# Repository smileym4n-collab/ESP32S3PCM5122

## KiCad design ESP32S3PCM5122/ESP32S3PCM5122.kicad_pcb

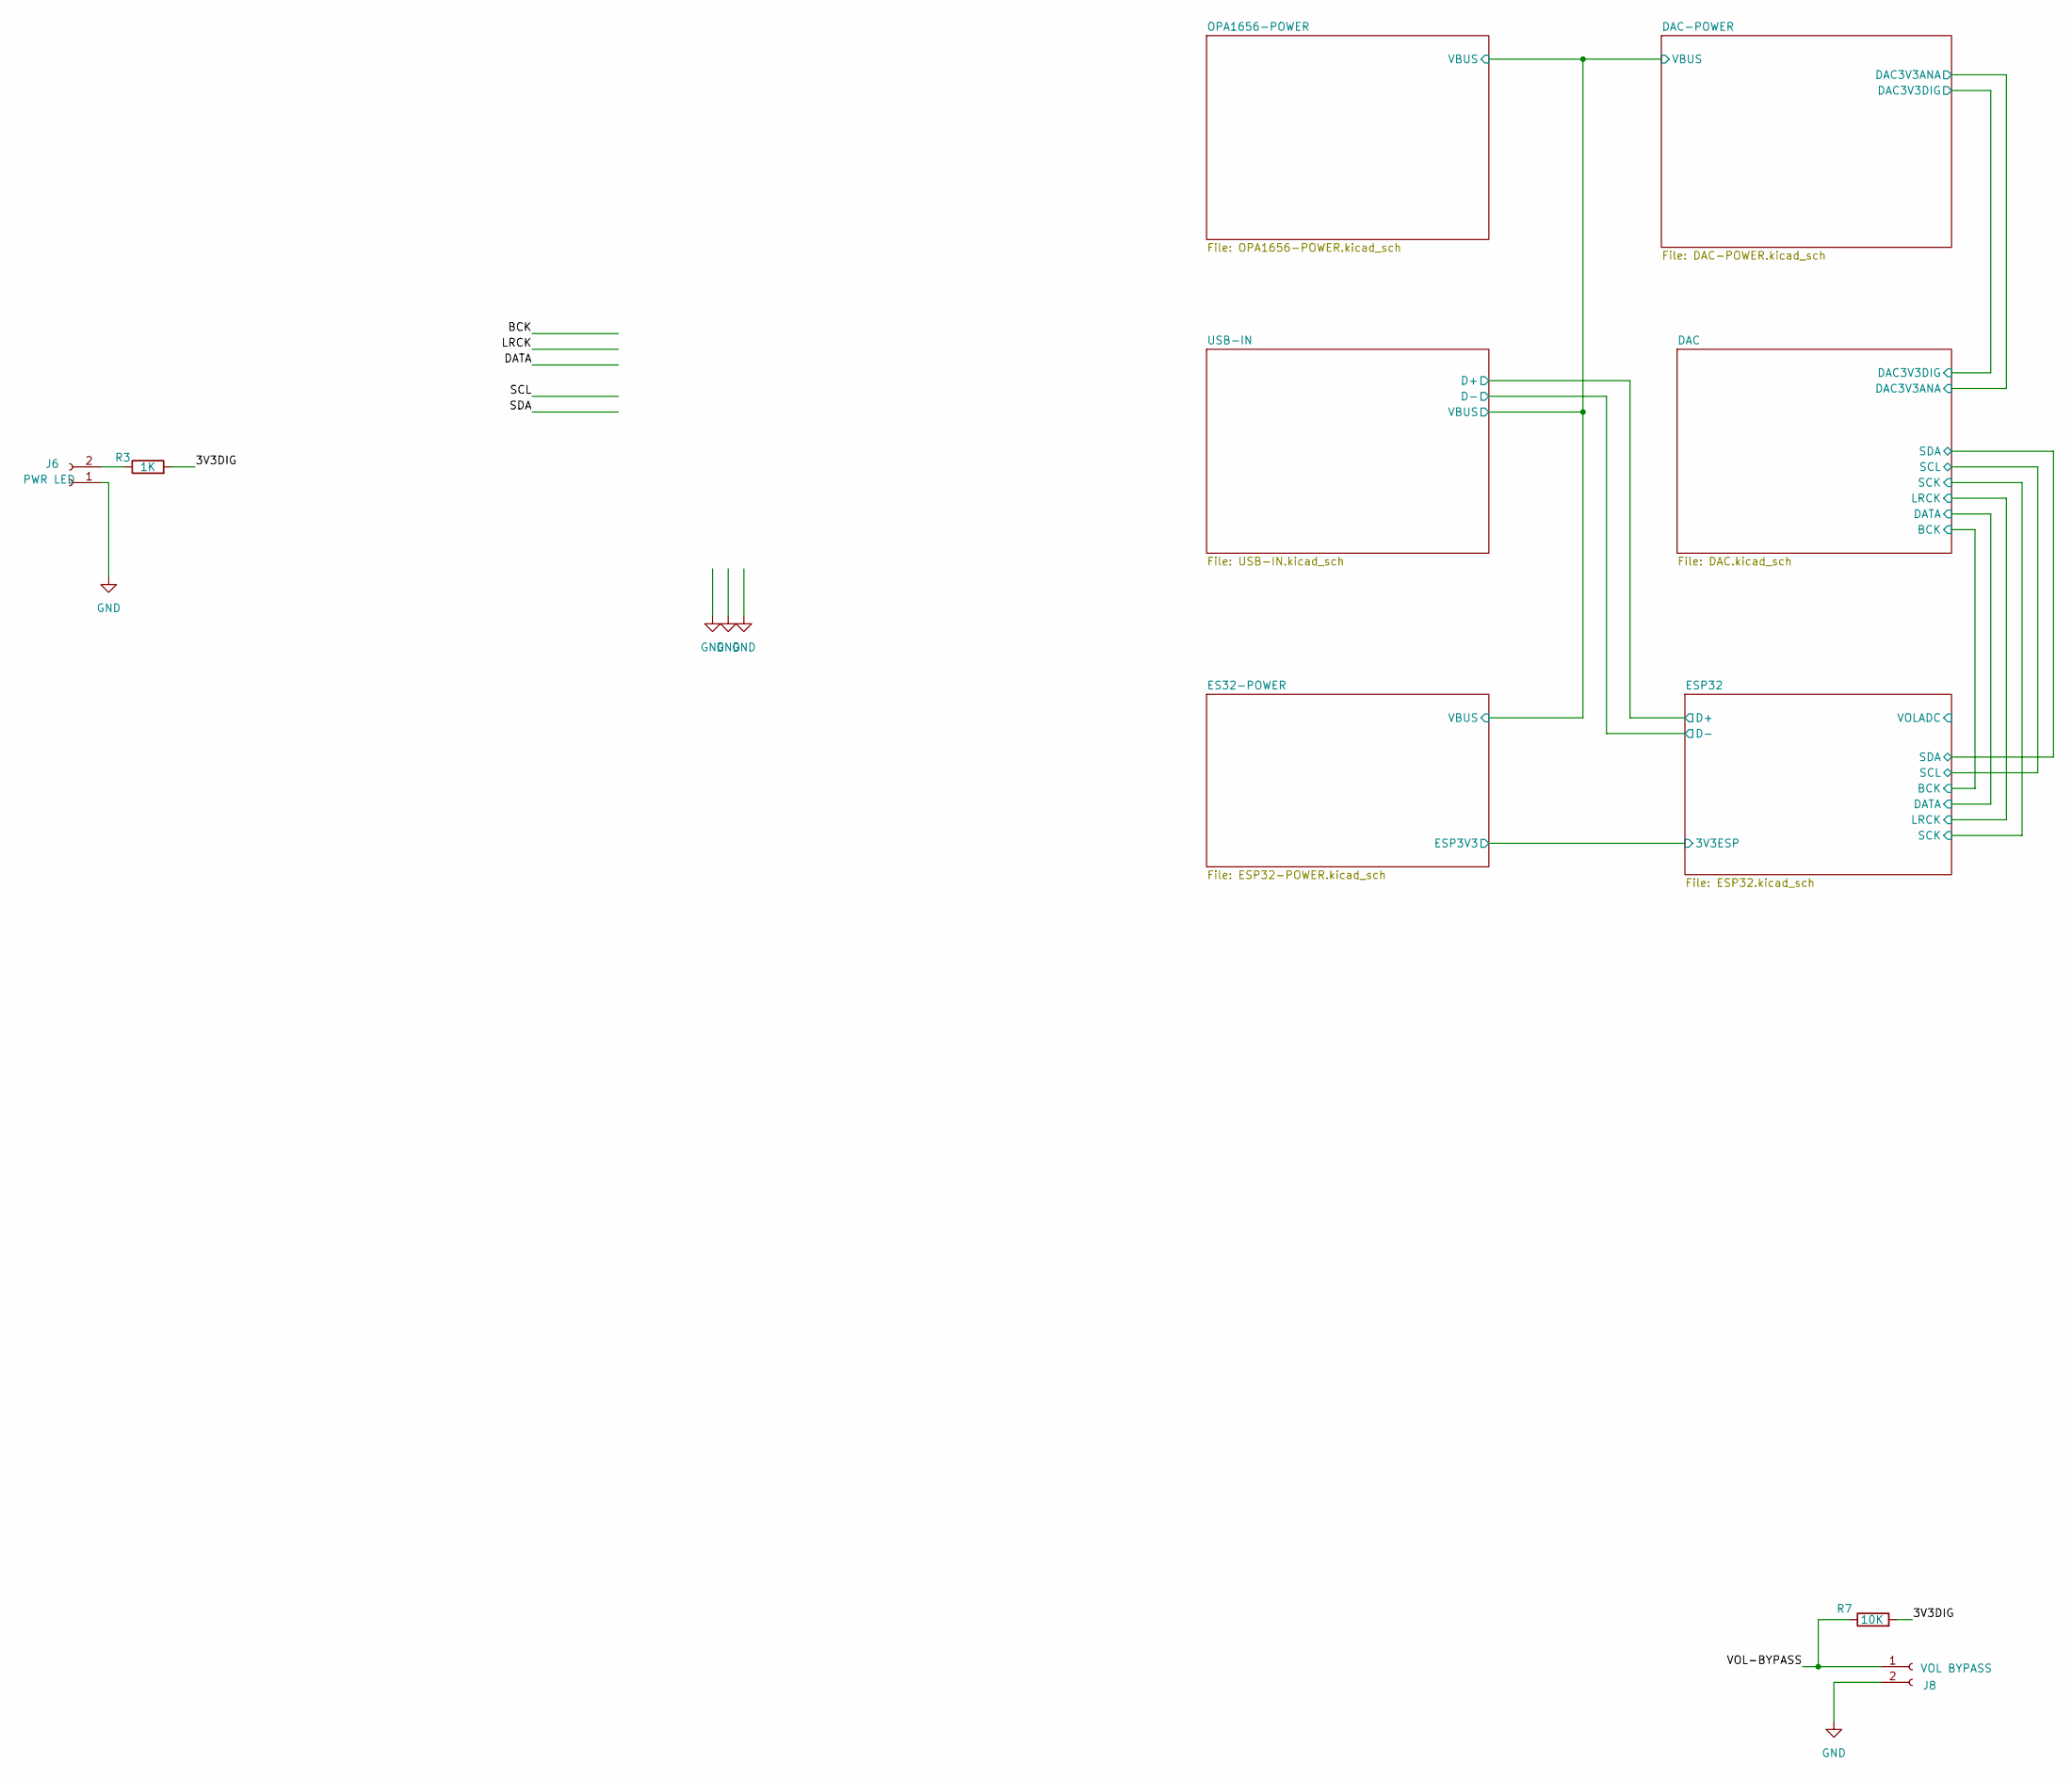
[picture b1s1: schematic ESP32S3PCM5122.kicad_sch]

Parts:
J6: PWR LED; JST_XH_B2B-XH-A_1x02_P2.50mm_Vertical
J8: VOL BYPASS; JST_XH_B2B-XH-A_1x02_P2.50mm_Vertical
R3: 1K; R_0805_2012Metric_Pad1.20x1.40mm_HandSolder
R7: 10K; R_0603_1608Metric_Pad0.98x0.95mm_HandSolder

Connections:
/3V3DIG: R3.2, R7.2
/VOL-BYPASS: J8.1, R7.1
GND: J6.1, J8.2; also elsewhere on the board
unnamed: J6.2, R3.1

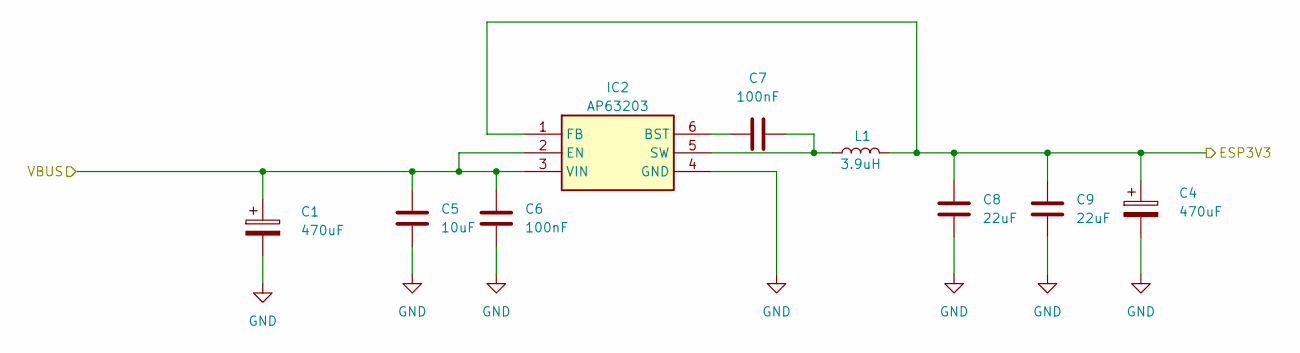
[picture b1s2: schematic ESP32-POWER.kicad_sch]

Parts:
C1, C4: 470uF; CP_Radial_D6.3mm_P2.50mm
C5: 10uF; C_1206_3216Metric_Pad1.33x1.80mm_HandSolder
C6, C7: 100nF; C_1206_3216Metric_Pad1.33x1.80mm_HandSolder
C8, C9: 22uF; C_0805_2012Metric_Pad1.18x1.45mm_HandSolder
IC2: AP63203; AP63205WU7; Manufacturer_Part_Number AP63205WU-7; Farnell Part Number 3518308
L1: 3.9uH; SRR4528A-3R9Y

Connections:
/DAC-POWER/VBUS: C1.1, C5.2, C6.2, IC2.2 (EN), IC2.3 (VIN); also elsewhere on the board
/ES32-POWER/ESP3V3: C4.1, C8.1, C9.1, IC2.1 (FB), L1.2; also elsewhere on the board
GND: C1.2, C4.2, C5.1, C6.1, C8.2, C9.2, IC2.4 (GND); also elsewhere on the board
unnamed: C7.1, IC2.6 (BST)
unnamed: C7.2, IC2.5 (SW), L1.1

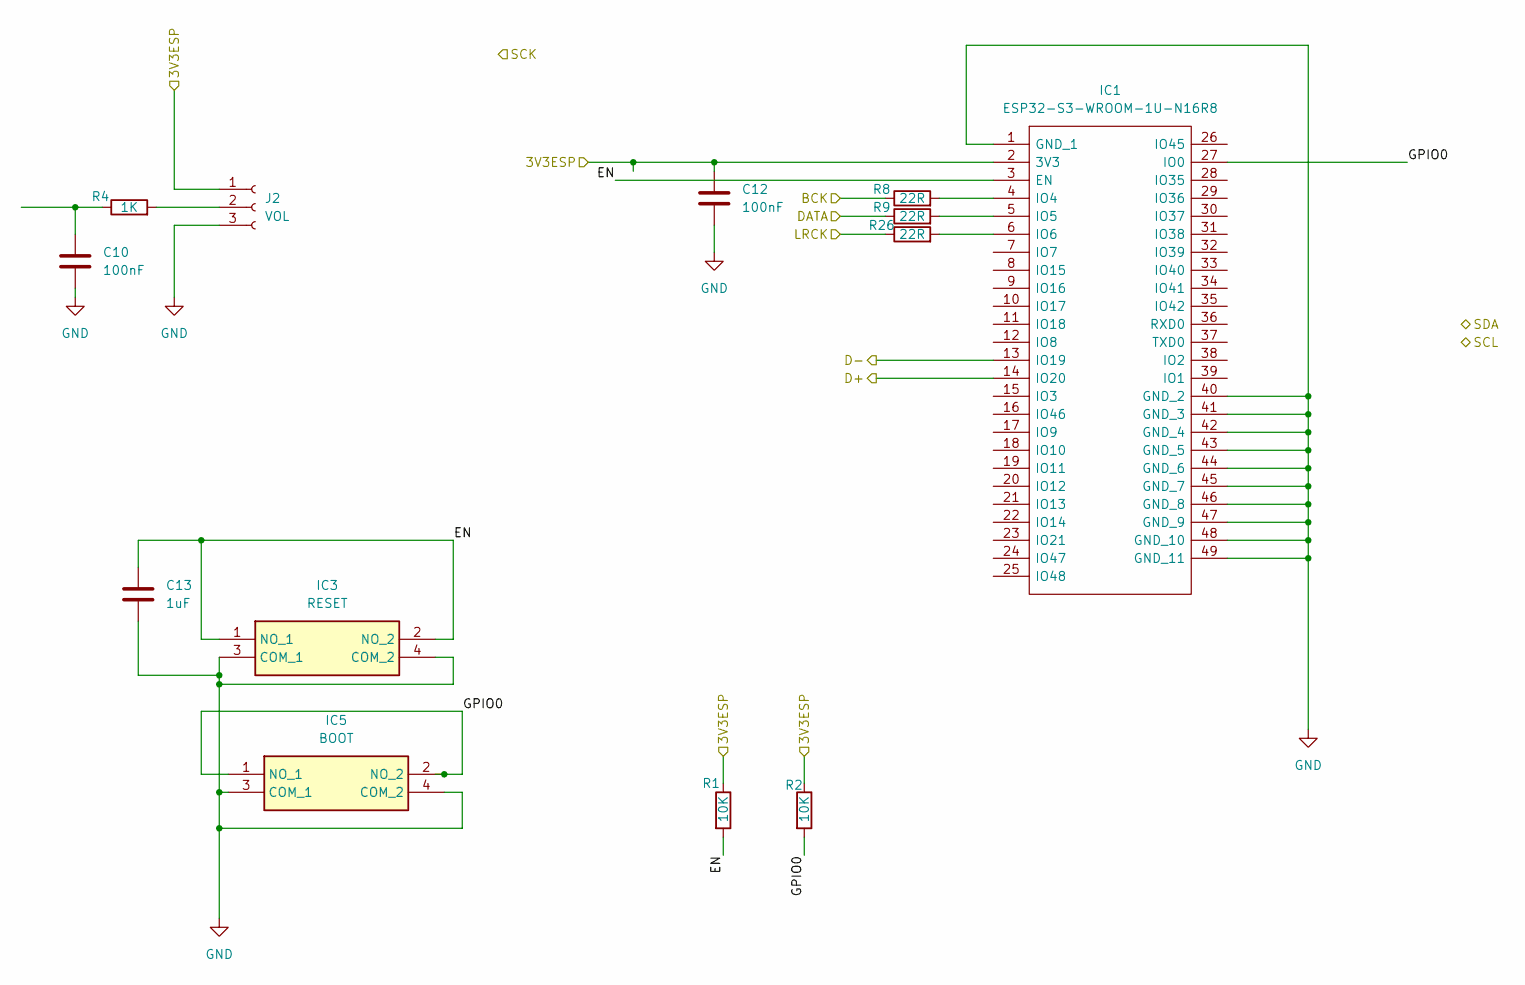
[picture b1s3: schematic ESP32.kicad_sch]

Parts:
C10, C12: 100nF; C_1206_3216Metric_Pad1.33x1.80mm_HandSolder
C13: 1uF; C_1206_3216Metric_Pad1.33x1.80mm_HandSolder
IC1: ESP32-S3-WROOM-1U-N16R8; ESP32S3WROOM1UN16R8; Mouser Part Number 356-ESP32S3WM1UN16R8
IC3: RESET; TS026650BK100SCRD; Mouser Part Number 179-TS026650BK100SCR
IC5: BOOT; TS026650BK100SCRD; Mouser Part Number 179-TS026650BK100SCR
J2: VOL; JST_XH_B3B-XH-A_1x03_P2.50mm_Vertical
R1, R2: 10K; R_0603_1608Metric_Pad0.98x0.95mm_HandSolder
R4: 1K; R_0805_2012Metric_Pad1.20x1.40mm_HandSolder
R8, R9, R26: 22R; R_0805_2012Metric_Pad1.20x1.40mm_HandSolder

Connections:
/DAC/BCK: R8.1; also elsewhere on the board
/DAC/DATA: R9.1; also elsewhere on the board
/DAC/LRCK: R26.1; also elsewhere on the board
/ES32-POWER/ESP3V3: C12.2, IC1.2 (3V3), J2.1, R1.1, R2.1; also elsewhere on the board
/ESP32/D+: IC1.14 (IO20); also elsewhere on the board
/ESP32/D-: IC1.13 (IO19); also elsewhere on the board
/ESP32/EN: C13.1, IC1.3 (EN), IC3.1 (NO_1), IC3.2 (NO_2), R1.2
/ESP32/GPIO0: IC1.27 (IO0), IC5.1 (NO_1), IC5.2 (NO_2), R2.2
GND: C10.1, C12.1, C13.2, IC1.1 (GND_1), IC1.40 (GND_2), IC1.41 (GND_3), IC1.42 (GND_4), IC1.43 (GND_5), IC1.44 (GND_6), IC1.45 (GND_7), IC1.46 (GND_8), IC1.47 (GND_9), IC1.48 (GND_10), IC1.49 (GND_11), IC3.3 (COM_1), IC3.4 (COM_2), IC5.3 (COM_1), IC5.4 (COM_2), J2.3; also elsewhere on the board
unnamed: C10.2, R4.1
unnamed: IC1.4 (IO4), R8.2
unnamed: IC1.5 (IO5), R9.2
unnamed: IC1.6 (IO6), R26.2
unnamed: J2.2, R4.2

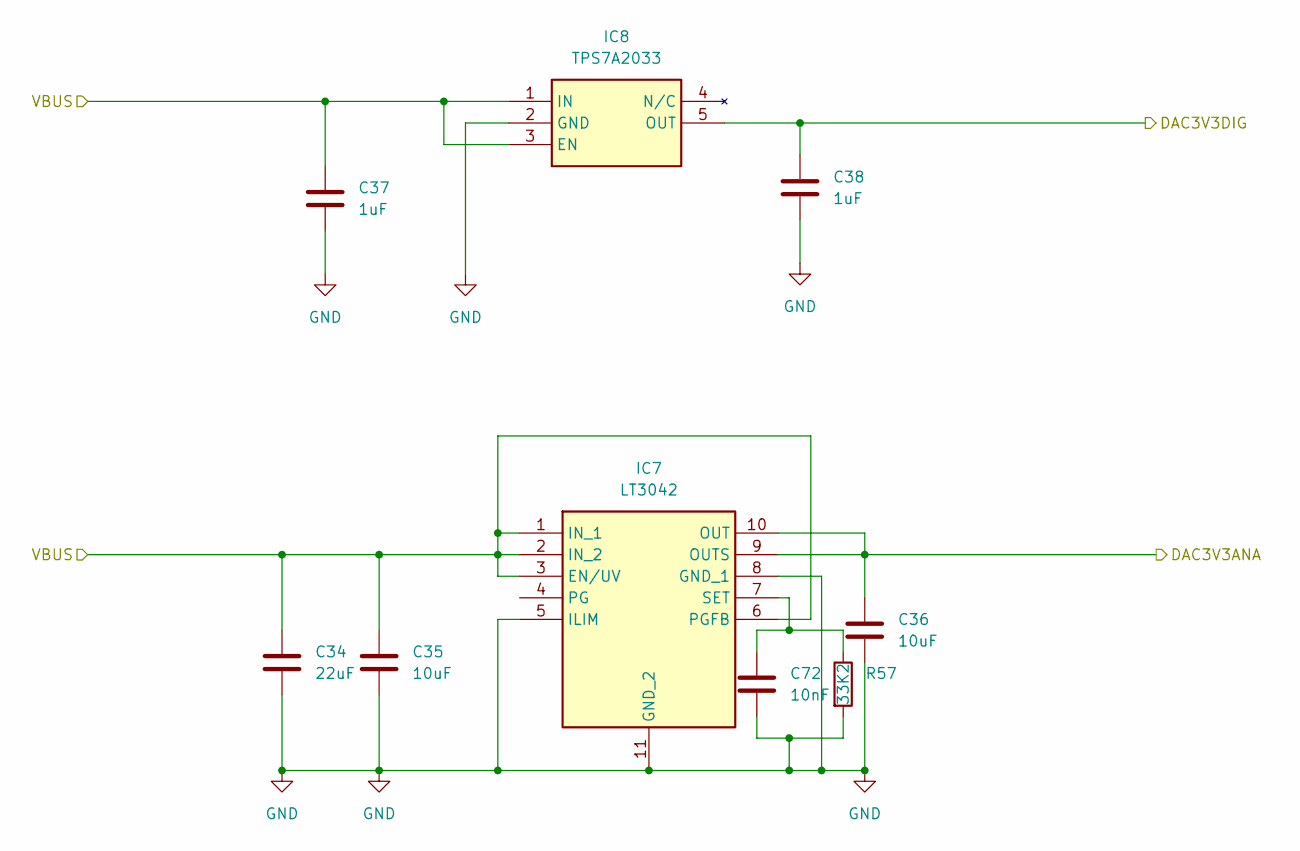
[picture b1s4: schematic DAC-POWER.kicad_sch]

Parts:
C34: 22uF; C_1206_3216Metric_Pad1.33x1.80mm_HandSolder
C35, C36: 10uF; C_0805_2012Metric_Pad1.18x1.45mm_HandSolder
C37, C38: 1uF; C_1206_3216Metric_Pad1.33x1.80mm_HandSolder
C72: 10nF; C_0805_2012Metric_Pad1.18x1.45mm_HandSolder
IC7: LT3042; Manufacturer_Part_Number LT3042EDD#TRPBF
IC8: TPS7A2033; SOT95P280X145-5N; Mouser Part Number 595-TPS7A2033PDBVR
R57: 33K2; R_0805_2012Metric_Pad1.20x1.40mm_HandSolder

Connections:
/DAC-POWER/DAC3V3ANA: C36.1, IC7.9 (OUTS), IC7.10 (OUT); also elsewhere on the board
/DAC-POWER/DAC3V3DIG: C38.1, IC8.5 (OUT); also elsewhere on the board
/DAC-POWER/VBUS: C34.1, C35.2, C37.1, IC7.1 (IN_1), IC7.2 (IN_2), IC7.3 (EN/UV), IC7.6 (PGFB), IC8.1 (IN), IC8.3 (EN); also elsewhere on the board
GND: C34.2, C35.1, C36.2, C37.2, C38.2, C72.2, IC7.5 (ILIM), IC7.8 (GND_1), IC7.11 (GND_2), IC8.2 (GND), R57.2; also elsewhere on the board
unnamed: C72.1, IC7.7 (SET), R57.1

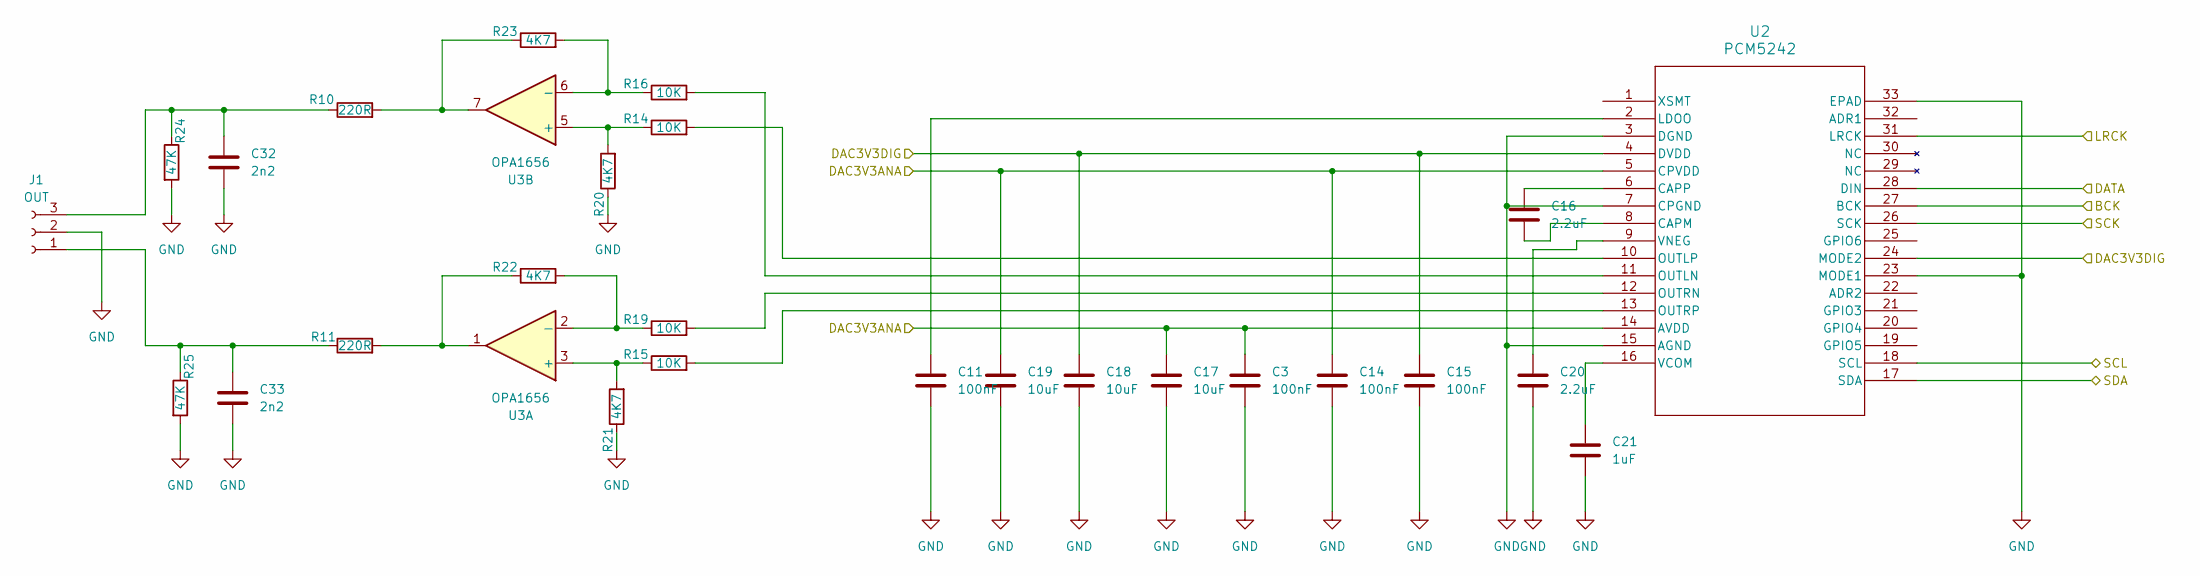
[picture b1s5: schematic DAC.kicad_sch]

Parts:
C3, C11, C14, C15: 100nF; C_1206_3216Metric_Pad1.33x1.80mm_HandSolder
C16, C20: 2.2uF; C_0805_2012Metric_Pad1.18x1.45mm_HandSolder
C17, C18, C19: 10uF; C_0805_2012Metric_Pad1.18x1.45mm_HandSolder
C21: 1uF; C_1206_3216Metric_Pad1.33x1.80mm_HandSolder
C32, C33: 2n2; C_0805_2012Metric_Pad1.18x1.45mm_HandSolder
J1: OUT; JST_XH_B3B-XH-A_1x03_P2.50mm_Vertical
R10, R11: 220R; R_0805_2012Metric_Pad1.20x1.40mm_HandSolder
R14, R15, R16, R19: 10K; R_0805_2012Metric_Pad1.20x1.40mm_HandSolder
R20, R21, R22, R23: 4K7; R_0805_2012Metric_Pad1.20x1.40mm_HandSolder
R24, R25: 47K; R_0805_2012Metric_Pad1.20x1.40mm_HandSolder
U2: PCM5242
U3: OPA1656; SOIC-8_3.9x4.9mm_P1.27mm

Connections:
/DAC-POWER/DAC3V3ANA: C3.1, C14.1, C17.1, C19.1, U2.5 (CPVDD), U2.14 (AVDD); also elsewhere on the board
/DAC-POWER/DAC3V3DIG: C15.1, C18.1, U2.4 (DVDD), U2.24 (MODE2); also elsewhere on the board
/DAC/BCK: U2.27 (BCK); also elsewhere on the board
/DAC/DATA: U2.28 (DIN); also elsewhere on the board
/DAC/LRCK: U2.31 (LRCK); also elsewhere on the board
/DAC/SCK: U2.26 (SCK)
/DAC/SCL: U2.18 (SCL)
/DAC/SDA: U2.17 (SDA)
GND: C3.2, C11.2, C14.2, C15.2, C17.2, C18.2, C19.2, C20.2, C21.2, C32.2, C33.2, J1.2, R20.1, R21.1, R24.2, R25.2, U2.3 (DGND), U2.7 (CPGND), U2.15 (AGND), U2.23 (MODE1), U2.33 (EPAD); also elsewhere on the board
unnamed: C33.1, J1.1, R11.1, R25.1
unnamed: C32.1, J1.3, R10.1, R24.1
unnamed: R10.2, R23.1, U3.7
unnamed: R11.2, R22.1, U3.1
unnamed: C16.2, U2.8 (CAPM)
unnamed: C16.1, U2.6 (CAPP)
unnamed: C11.1, U2.2 (LDOO)
unnamed: R16.2, U2.11 (OUTLN)
unnamed: R14.2, U2.10 (OUTLP)
unnamed: R19.2, U2.12 (OUTRN)
unnamed: R15.2, U2.13 (OUTRP)
unnamed: C21.1, U2.16 (VCOM)
unnamed: C20.1, U2.9 (VNEG)
unnamed: R15.1, R21.2, U3.3 (+)
unnamed: R19.1, R22.2, U3.2 (-)
unnamed: R14.1, R20.2, U3.5 (+)
unnamed: R16.1, R23.2, U3.6 (-)

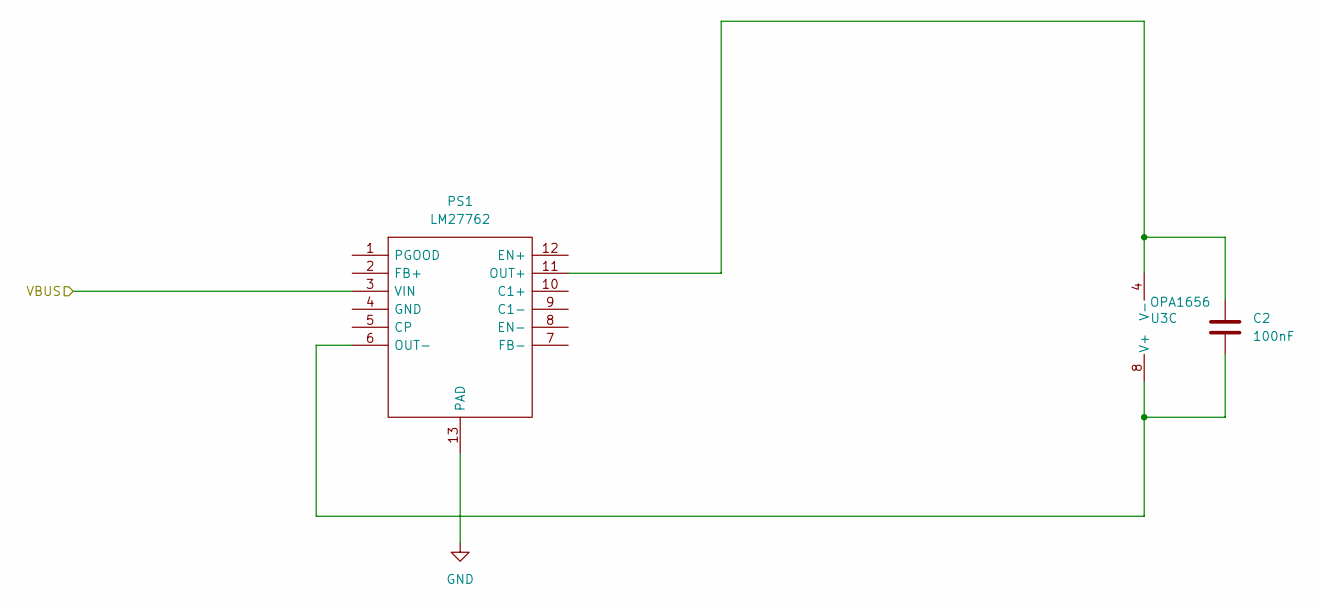
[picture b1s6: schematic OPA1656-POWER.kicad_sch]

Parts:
C2: 100nF; C_1206_3216Metric_Pad1.33x1.80mm_HandSolder
PS1: LM27762; LM27762DSSR; Mouser Part Number 595-LM27762DSSR
U3: OPA1656; SOIC-8_3.9x4.9mm_P1.27mm

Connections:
/DAC-POWER/VBUS: PS1.3 (VIN); also elsewhere on the board
GND: PS1.13 (PAD); also elsewhere on the board
unnamed: C2.1, PS1.11 (OUT+), U3.4 (V-)
unnamed: C2.2, PS1.6 (OUT-), U3.8 (V+)

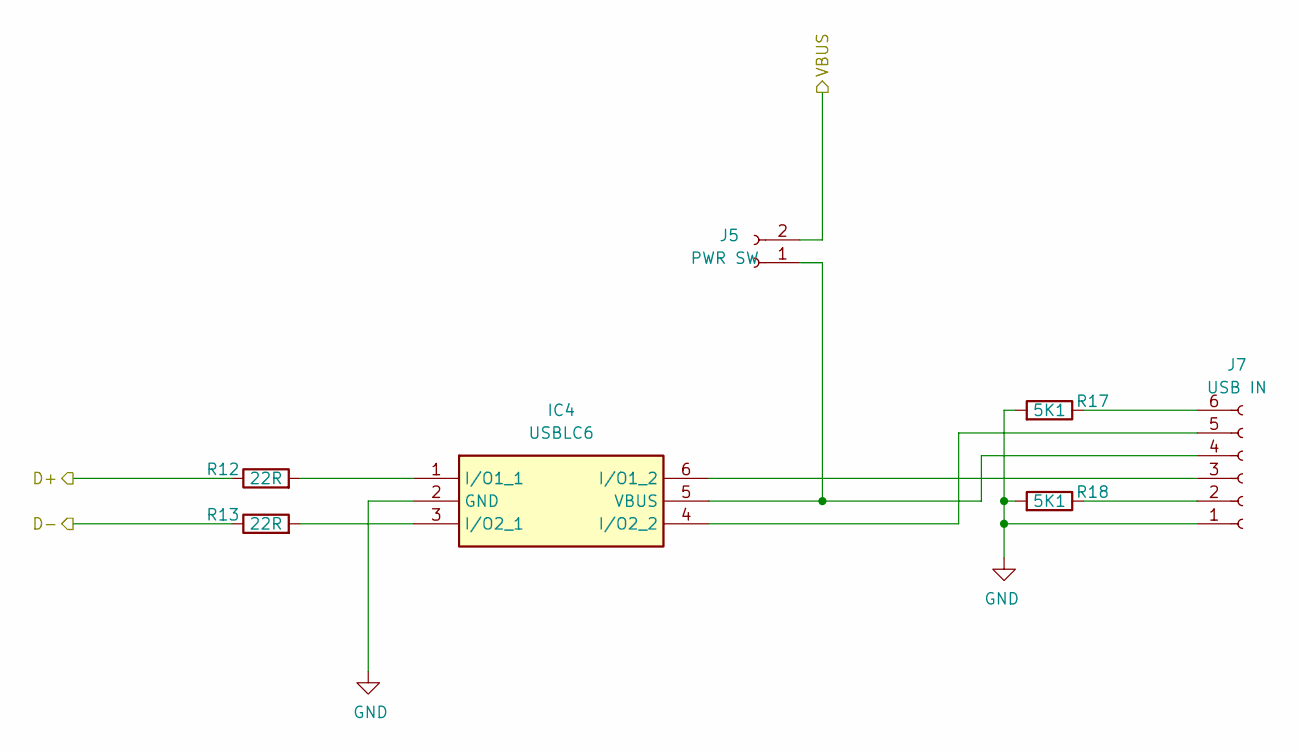
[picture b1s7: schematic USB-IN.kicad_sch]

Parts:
IC4: USBLC6; SOT-23-6_Handsoldering; Mouser Part Number 511-USBLC6-2SC6
J5: PWR SW; JST_XH_B2B-XH-A_1x02_P2.50mm_Vertical
J7: USB IN; JST_XH_B6B-XH-A_1x06_P2.50mm_Vertical
R12, R13: 22R; R_0805_2012Metric_Pad1.20x1.40mm_HandSolder
R17, R18: 5K1; R_0805_2012Metric_Pad1.20x1.40mm_HandSolder

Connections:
/DAC-POWER/VBUS: J5.2; also elsewhere on the board
/ESP32/D+: R12.1; also elsewhere on the board
/ESP32/D-: R13.1; also elsewhere on the board
GND: IC4.2 (GND), J7.1, R17.2, R18.2; also elsewhere on the board
unnamed: IC4.1 (I/O1_1), R12.2
unnamed: IC4.6 (I/O1_2), J7.3
unnamed: IC4.3 (I/O2_1), R13.2
unnamed: IC4.4 (I/O2_2), J7.5
unnamed: IC4.5 (VBUS), J5.1, J7.4
unnamed: J7.2, R18.1
unnamed: J7.6, R17.1

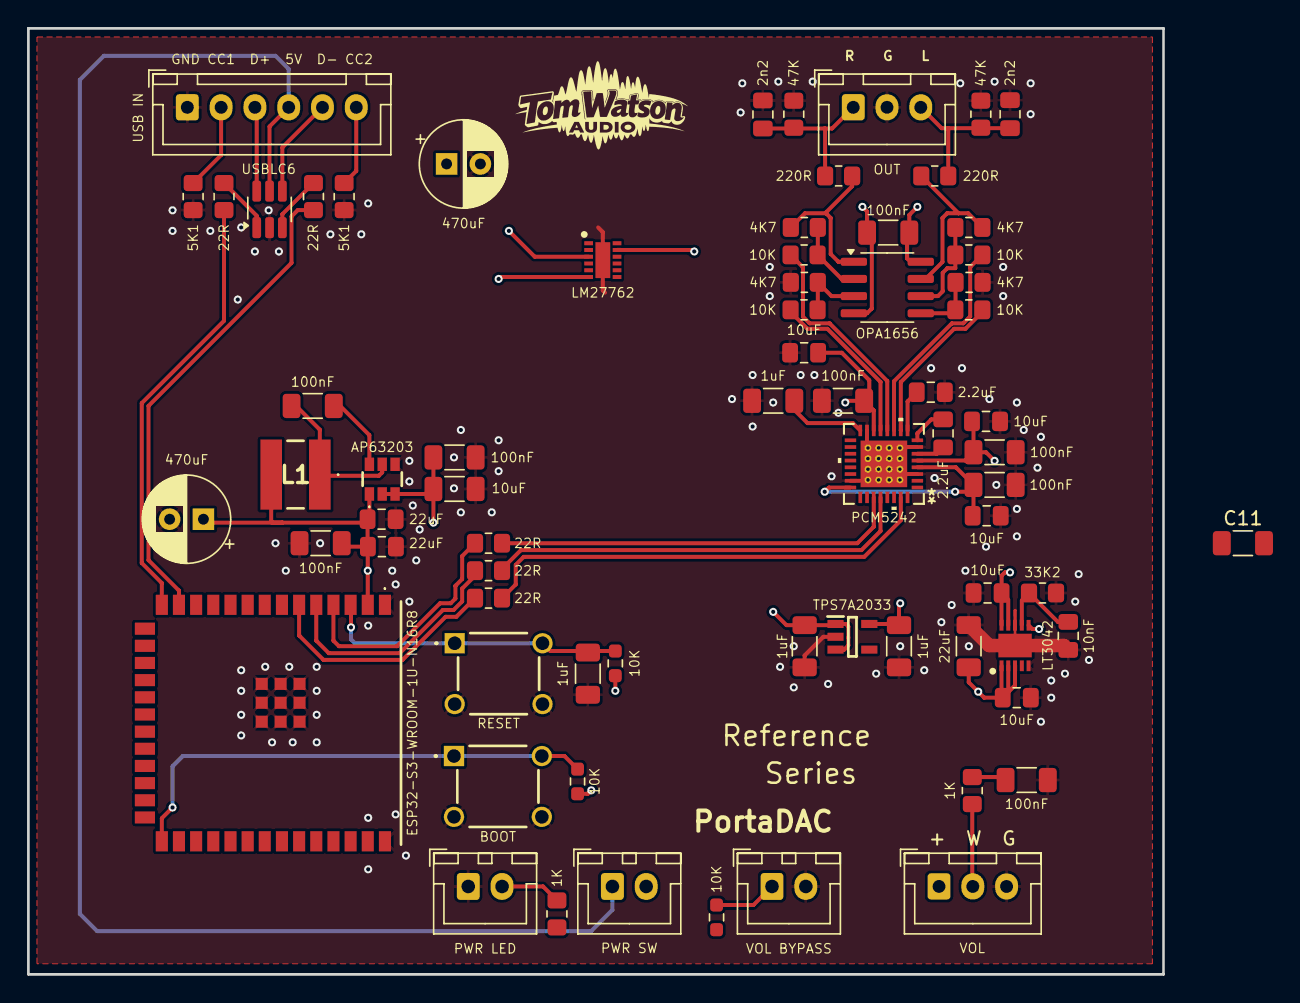
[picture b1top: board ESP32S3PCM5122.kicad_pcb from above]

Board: 4 copper layers, 84.0 x 70.0 mm, 71 parts (0 on the bottom side), 49 nets.

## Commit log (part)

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2026-06-16 initial
2026-06-18 move to PCM5242
2026-06-19 more work
